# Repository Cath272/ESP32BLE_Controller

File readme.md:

## Introduction

ESP32BLE_Controller is a ESP32 based project that aimes to make an affortable controller.

The project idea came around when i wanted to incorporate pcb design with a esp32 microcontroller.
The controller uses the [ESP32-BLE-CompositeHID library](https://github.com/Mystfit/ESP32-BLE-CompositeHID) and can be used on any Bluetooth device that can accept xinput devices.

## General description

The player turns on the controller and connects it to a pc/phone and it just works as a XINPUT device and can control any game/sofware that implements the xinput API

### Block diagram

## Hardware Design

### ESP32 Wroom Module
  This project is based on the ESP32-WROOM-32 Module that incorporates an Espressif ESP32 Dual Core 32bit microcontroller with 4MB of Flash Storage, an crystal oscilator, decoupling capacitors and an 2.4Ghz Antena for Wi-Fi and Bluetooth.
  I have chosen this module beacause of it's ease of use, the familiarity i have with it and it low price (around 2.5EUR).  
  
### USB C 14pin port
  USB port for programing and for providing 5V power. It uses 2 5.1K resistors on the CC lines so it can use USB PD and request 5V from it. (Aka use a Type C to Type C cable)
### TPS63020 - High Efficiency Single Inductor Buck-Boost Converter
  Buck Boost Converter that converts 5V from USB to the 3.3V used by the Wroom Module and the CH343p Ic. It also needs an 1.5uH Inductor and filtering caps on the input and output. I chose this Ic because of its High Efficiency. 

### CH343P USB to High-Speed Serial Chip
  USB to High Speed Serial Ic for programming the ESP32. It is made by WCH and i mainly chose it beacause of its small form QFN package and its low price. 

### 10 Buttons
  10 SMD Buttons connected to GPIOs of the ESP32. 
### 2 BC817 Transistors
  2 Transistors used for the auto programming circuit
  
### 2 LEDS (RED for Power and BLUE IO2 configurable)
  
### Schematic:

### Bill of materials 
| Component           |         Image                                                                                         |         Model  |           Pcs | Price           | Link          |
| -------------       |                                                                                        -------------  | -------------  | ------------- | --------------- | ------------- |
| ESP32 Wroom Module  |          | ESP32-WROOM-32 | 1             | 2.5EUR          |   [Aliexpress](https://www.aliexpress.com/item/1005006579469362.html?spm=a2g0o.order_list.order_list_main.5.1cc41802YGhEhy)  |
| USB C 16pin port    |           | USB C 16 PIN   | 1             | 4.85EUR/100Pcs, 0.05EUR/1Pcs | [Aliexpress](https://www.aliexpress.com/item/1005006072023656.html?spm=a2g0o.order_list.order_list_main.27.1cc41802YGhEhy) |
|Buck Boost Coverter  |        |   TPS63020     | 1             | 3.5EU10/Pcs 0.35EUR/Pcs          | [Aliexpress](https://www.aliexpress.com/item/1005006228616468.html?spm=a2g0o.order_list.order_list_main.76.1cc41802YGhEhy) |
|USB To Serial        |             | CH343P         | 1             | 8EUR/10Pcs, 0.8EUR/1Pcs       | [Aliexpress](https://www.aliexpress.com/item/1005006879961854.html?spm=a2g0o.order_list.order_list_main.81.1cc41802YGhEhy) |       
|Buttons              |            | Metal Dome 3.7*3.7*0.35mm | 10 | 1.5EUR/10Pcs          | [Aliexpress](https://www.aliexpress.com/item/4001125555481.html?spm=a2g0o.order_list.order_list_main.90.1cc41802YGhEhy) |
|NPN Transistor       |               |   BC817        | 2             | 1.5EUR/100PCs, 0.015EUR/Pcs    | [Aliexpress](https://www.aliexpress.com/item/4001032215515.html?spm=a2g0o.order_list.order_list_main.138.1cc41802YGhEhy) |

Other Components are from Components Sample Books that include many values of [Resistors](https://www.aliexpress.com/item/1005006169072137.html?spm=a2g0o.order_list.order_list_main.185.1cc41802YGhEhy), [LEDs](https://www.aliexpress.com/item/1005003580299883.html?spm=a2g0o.order_list.order_list_main.174.1cc41802YGhEhy) and [Capacitors](https://www.aliexpress.com/item/1005005456060166.html?spm=a2g0o.order_list.order_list_main.178.1cc41802YGhEhy) that i bought before.

###PCB

The PCB was created by me, using KICAD 8.0

Front:

Back:

## Software Design

The program is simple and just reads what buttons are pressed and send the matching XINPUT mapped button through bluetooth to the connected device.
The Program is centered around the [ESP32-BLE-CompositeHID library](https://github.com/Mystfit/ESP32-BLE-CompositeHID) and a specific version of [NimBLE-Arduino](https://github.com/h2zero/NimBLE-Arduino) (Not needed anymore as the CompositeHID library was updated recently).
I used the ESP32-BLE-CompositeHID library because i wanted it to work seamlessly with any windows device, as it just sees it as an Xbox Controller, and windows has xbox controller drivers built in. No need for Steam mapping or any other software.
The Project uses buttons, an led for showing that it conected to the pc and it uses Serial to print any pressed button.

## Results

[Video demonstration](https://storage.rcs-rds.ro/links/72c412c2-119c-4140-a43d-5230902e5003)

## Resources
[ESP32-BLE-CompositeHID library](https://github.com/Mystfit/ESP32-BLE-CompositeHID)

[NimBLE-Arduino](https://github.com/h2zero/NimBLE-Arduino)

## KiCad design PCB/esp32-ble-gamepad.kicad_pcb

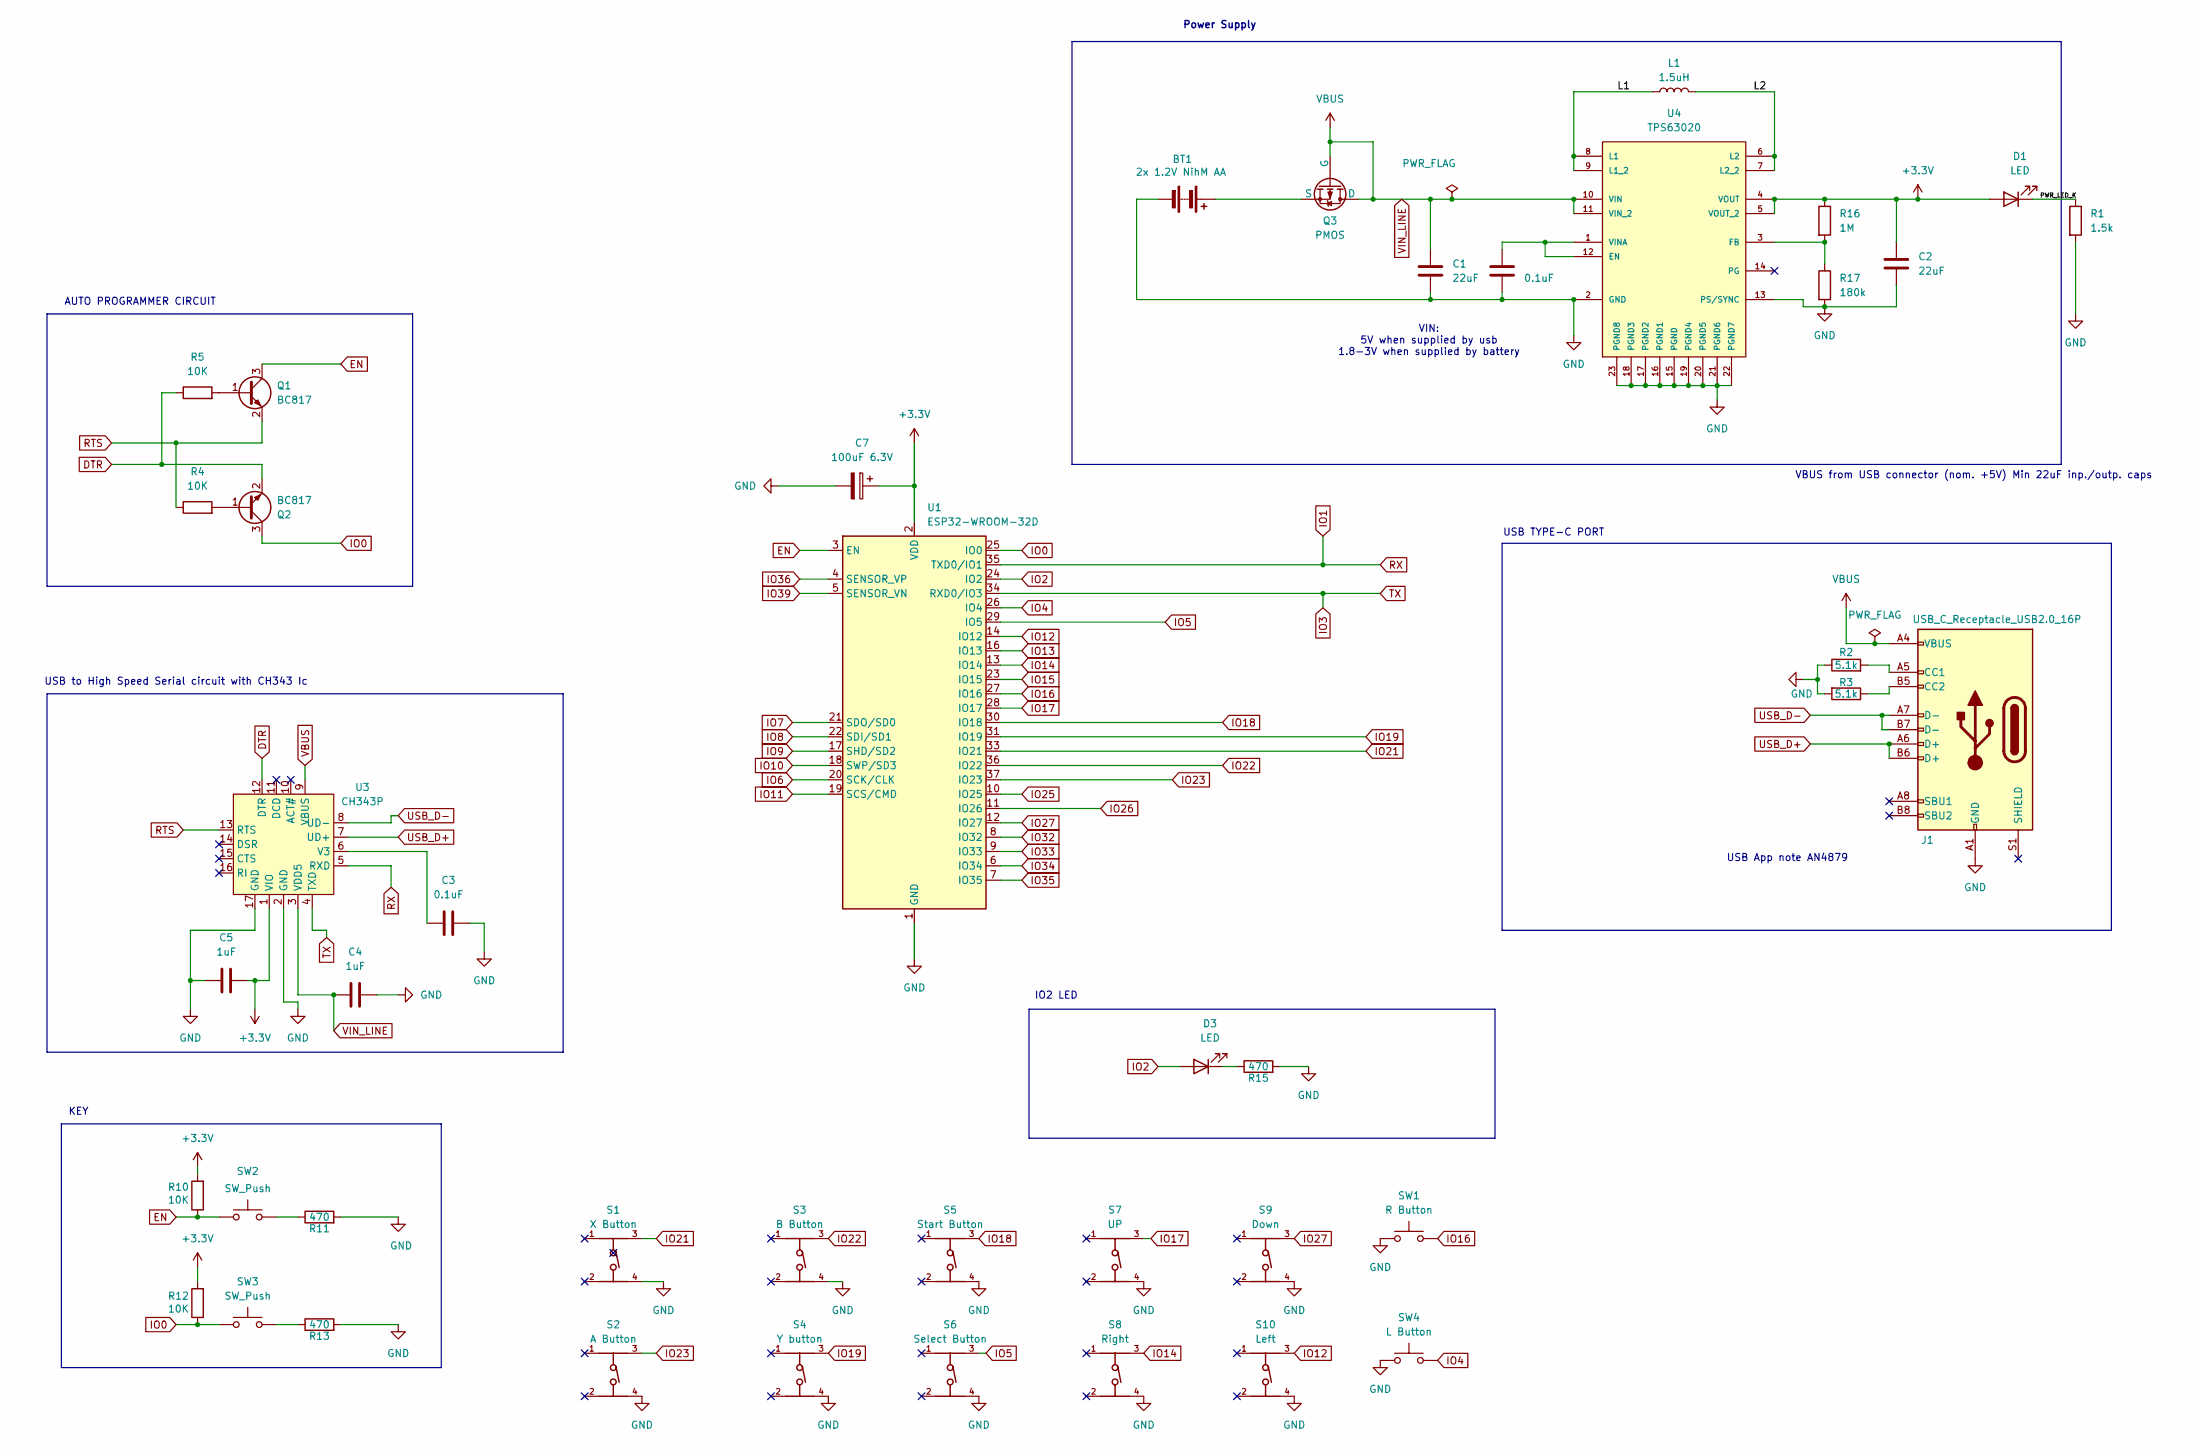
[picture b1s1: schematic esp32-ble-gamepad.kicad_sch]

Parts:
BT1: 2x 1.2V NihM AA; PinSocket_1x02_P2.54mm_Vertical
C1, C2: 22uF; C_0805_2012Metric
C3, C10: 0.1uF; C_0402_1005Metric
C4, C5: 1uF; C_0402_1005Metric
C7: 100uF 6.3V; CP_EIA-3528-15_AVX-H_Pad1.50x2.35mm_HandSolder
D1, D3: LED; LED_0603_1608Metric
J1: USB_C_Receptacle_USB2.0_16P; USB_C_Receptacle_GCT_USB4105-xx-A_16P_TopMnt_Horizontal
L1: 1.5uH; L_6.3x6.3_H3
Q1, Q2: BC817; SOT-23
Q3: PMOS; TSOT-23_HandSoldering
R1: 1.5k; R_0402_1005Metric
R2, R3: 5.1k; R_0402_1005Metric
R4, R5, R10, R12: 10K; R_0402_1005Metric
R11, R13, R15: 470; R_0402_1005Metric
R16: 1M; R_0402_1005Metric
R17: 180k; R_0402_1005Metric
S1: X Button; 430173003816; PART-NUMBER 430173003816
S2: A Button; 430173003816; PART-NUMBER 430173003816
S3: B Button; 430173003816; PART-NUMBER 430173003816
S4: Y button; 430173003816; PART-NUMBER 430173003816
S5: Start Button; 430173003816; PART-NUMBER 430173003816
S6: Select Button; 430173003816; PART-NUMBER 430173003816
S7: UP; 430173003816; PART-NUMBER 430173003816
S8: Right; 430173003816; PART-NUMBER 430173003816
S9: Down; 430173003816; PART-NUMBER 430173003816
S10: Left; 430173003816; PART-NUMBER 430173003816
SW1: R Button; SW_Tactile_SKHH_Angled
SW2, SW3: SW_Push; SW_SPST_PTS810
SW4: L Button; SW_Tactile_SKHH_Angled
U1: ESP32-WROOM-32D
U3: CH343P; TQFN-16-1EP_3x3mm_P0.5mm_EP1.6x1.6mm
U4: TPS63020; QFN14-3X4MM

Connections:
+3.3V: C2.1, C5.2, C7.1, D1.2 (A), R10.2, R12.2, R16.1, U1.2 (VDD), U3.1 (VIO), U4.4 (VOUT), U4.5 (VOUT_2)
/L1: L1.1, U4.8 (L1), U4.9 (L1_2)
/L2: L1.2, U4.6 (L2), U4.7 (L2_2)
/PWR_LED_K: D1.1 (K), R1.1
DTR: Q2.2 (E), R5.1, U3.12 (DTR)
EN: Q1.3 (C), R10.1, SW2.1, U1.3 (EN)
GND: BT1.2 (-), C1.2, C2.2, C3.2, C4.2, C5.1, C7.2, C10.1, J1.A1 (GND), J1.A12 (GND), J1.B1 (GND), J1.B12 (GND), R1.2, R2.1, R3.2, R11.2, R13.2, R15.2, R17.2, S1.4, S2.4, S3.4, S4.4, S5.4, S6.4, S7.4, S8.4, S9.4, S10.4, SW1.1, SW4.1, U1.1 (GND), U1.15 (GND), U1.38 (GND), U1.39 (GND), U3.2 (GND), U3.17 (GND), U4.2 (GND), U4.13 (PS/SYNC), U4.15 (PGND), U4.16 (PGND1), U4.17 (PGND2), U4.18 (PGND3), U4.19 (PGND4), U4.20 (PGND5), U4.21 (PGND6), U4.22 (PGND7), U4.23 (PGND8)
IO0: Q2.3 (C), R12.1, SW3.1, U1.25 (IO0)
IO1: U1.35 (TXD0/IO1), U3.5 (RXD)
IO2: D3.2 (A), U1.24 (IO2)
IO3: U1.34 (RXD0/IO3), U3.4 (TXD)
IO4: SW4.2, U1.26 (IO4)
IO5: S6.3, U1.29 (IO5)
IO6: U1.20 (SCK/CLK)
IO7: U1.21 (SDO/SD0)
IO8: U1.22 (SDI/SD1)
IO9: U1.17 (SHD/SD2)
IO10: U1.18 (SWP/SD3)
IO11: U1.19 (SCS/CMD)
IO12: S10.3, U1.14 (IO12)
IO13: U1.16 (IO13)
IO14: S8.3, U1.13 (IO14)
IO15: U1.23 (IO15)
IO16: SW1.2, U1.27 (IO16)
IO17: S7.3, U1.28 (IO17)
IO18: S5.3, U1.30 (IO18)
IO19: S4.3, U1.31 (IO19)
IO21: S1.3, U1.33 (IO21)
IO22: S3.3, U1.36 (IO22)
IO23: S2.3, U1.37 (IO23)
IO25: U1.10 (IO25)
IO26: U1.11 (IO26)
IO27: S9.3, U1.12 (IO27)
IO32: U1.8 (IO32)
IO33: U1.9 (IO33)
IO34: U1.6 (IO34)
IO35: U1.7 (IO35)
IO36: U1.4 (SENSOR_VP)
IO39: U1.5 (SENSOR_VN)
unnamed: BT1.1 (+), Q3.2 (S)
unnamed: D3.1 (K), R15.1
unnamed: J1.A5 (CC1), R2.2
unnamed: J1.B5 (CC2), R3.1
unnamed: Q1.1 (B), R5.2
unnamed: Q2.1 (B), R4.2
unnamed: R11.1, SW2.2
unnamed: R13.1, SW3.2
unnamed: C3.1, U3.6 (V3)
unnamed: C10.2, U4.1 (VINA), U4.12 (EN)
unnamed: R16.2, R17.1, U4.3 (FB)
RTS: Q1.2 (E), R4.1, U3.13 (RTS)
USB_D+: J1.A6 (D+), J1.B6 (D+), U3.7 (UD+)
USB_D-: J1.A7 (D-), J1.B7 (D-), U3.8 (UD-)
VBUS: C1.1, C4.1, J1.A4 (VBUS), J1.A9 (VBUS), J1.B4 (VBUS), J1.B9 (VBUS), Q3.1 (G), Q3.3 (D), U3.3 (VDD5), U3.9 (VBUS), U4.10 (VIN), U4.11 (VIN_2)

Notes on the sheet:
KEY
IO2 LED
USB to High Speed Serial circuit with CH343 Ic
AUTO PROGRAMMER CIRCUIT
VIN: 5V when supplied by usb 1.8-3V when supplied by battery
VBUS from USB connector (nom. +5V) Min 22uF inp./outp. caps
USB App note AN4879
Power Supply
USB TYPE-C PORT

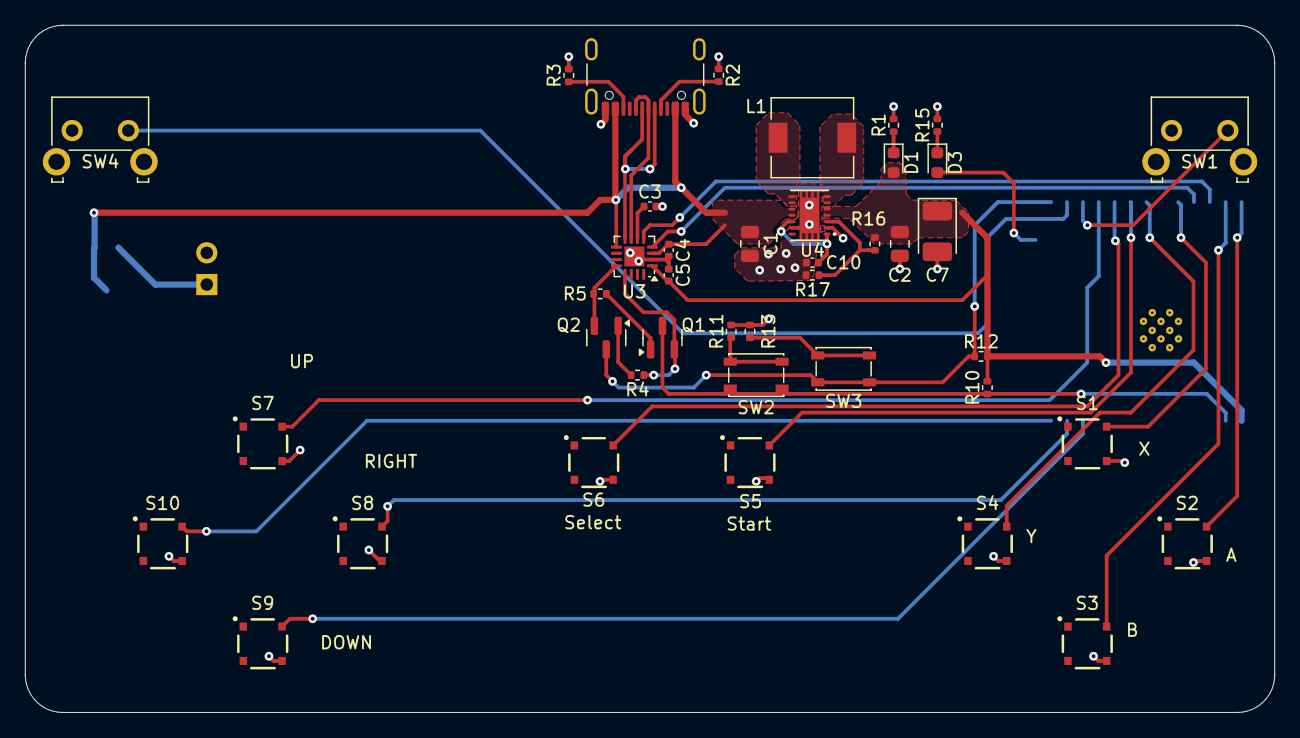
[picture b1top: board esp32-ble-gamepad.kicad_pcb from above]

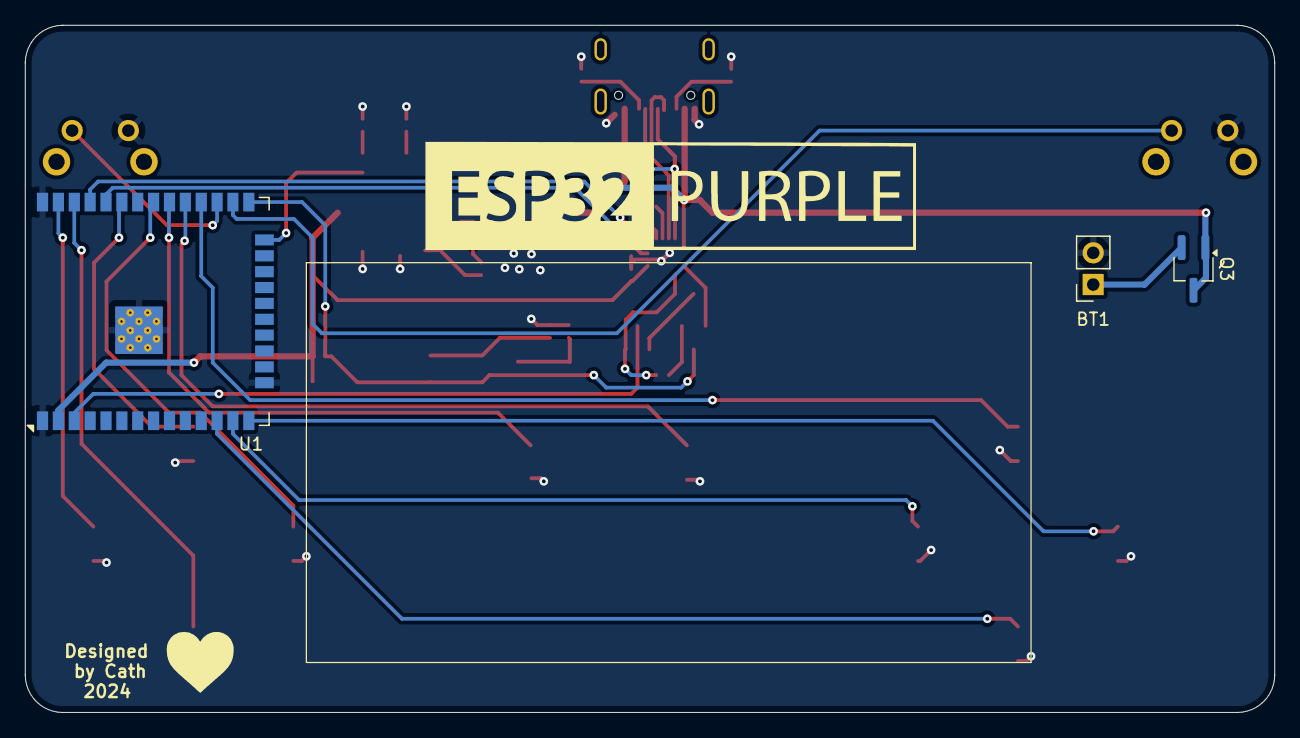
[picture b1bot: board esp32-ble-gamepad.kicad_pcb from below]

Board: 2 copper layers, 100.0 x 55.0 mm, 44 parts (3 on the bottom side), 38 nets.

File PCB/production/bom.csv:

Designator,Footprint,Quantity,Value,LCSC Part #
BT1,PinSocket_1x02_P2.54mm_Vertical,1,2x 1.2V NihM AA,
"C1, C2",0805,2,22uF,
"C10, C3",0402,2,0.1uF,
"C4, C5",0402,2,1uF,
C7,CP_EIA-3528-15_AVX-H_Pad1.50x2.35mm_HandSolder,1,100uF 6.3V,
"D1, D3",0603,2,LED,
J1,USB_C_Receptacle_GCT_USB4105-xx-A_16P_TopMnt_Horizontal,1,USB_C_Receptacle_USB2.0_16P,
L1,L_6.3x6.3_H3,1,1.5uH,
"Q1, Q2",SOT-23,2,BC817,
Q3,TSOT-23_HandSoldering,1,PMOS,
R1,0402,1,1.5k,
"R10, R12, R4, R5",0402,4,10K,
"R11, R13, R15",0402,3,470,
R16,0402,1,1M,
R17,0402,1,180k,
"R2, R3",0402,2,5.1k,
S1,430173003816,1,X Button,
S10,430173003816,1,Left,
S2,430173003816,1,A Button,
S3,430173003816,1,B Button,
S4,430173003816,1,Y button,
S5,430173003816,1,Start Button,
S6,430173003816,1,Select Button,
S7,430173003816,1,UP,
S8,430173003816,1,Right,
S9,430173003816,1,Down,
SW1,SW_Tactile_SKHH_Angled,1,R Button,
"SW2, SW3",SW_SPST_PTS810,2,SW_Push,
SW4,SW_Tactile_SKHH_Angled,1,L Button,
U1,ESP32-WROOM-32D,1,ESP32-WROOM-32D,
U3,TQFN-16-1EP_3x3mm_P0.5mm_EP1.6x1.6mm,1,CH343P,
U4,QFN14-3X4MM,1,TPS63020,
